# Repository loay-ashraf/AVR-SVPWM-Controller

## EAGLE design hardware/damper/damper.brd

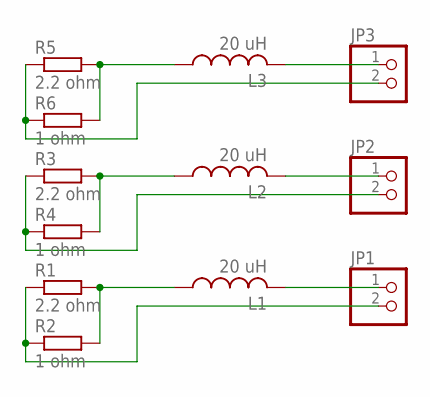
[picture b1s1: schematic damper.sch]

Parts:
JP1, JP2, JP3: PINHD-1X2; 1X02
L1, L2, L3: 20 uH; 0207/10
R1, R3, R5: 2.2 ohm; VTA52
R2, R4, R6: 1 ohm; VTA52

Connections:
unnamed: L1.1, R1.2, R2.2
unnamed: JP1.1, L1.2
unnamed: JP1.2, R1.1, R2.1
unnamed: L2.1, R3.2, R4.2
unnamed: JP2.1, L2.2
unnamed: JP2.2, R3.1, R4.1
unnamed: L3.1, R5.2, R6.2
unnamed: JP3.1, L3.2
unnamed: JP3.2, R5.1, R6.1

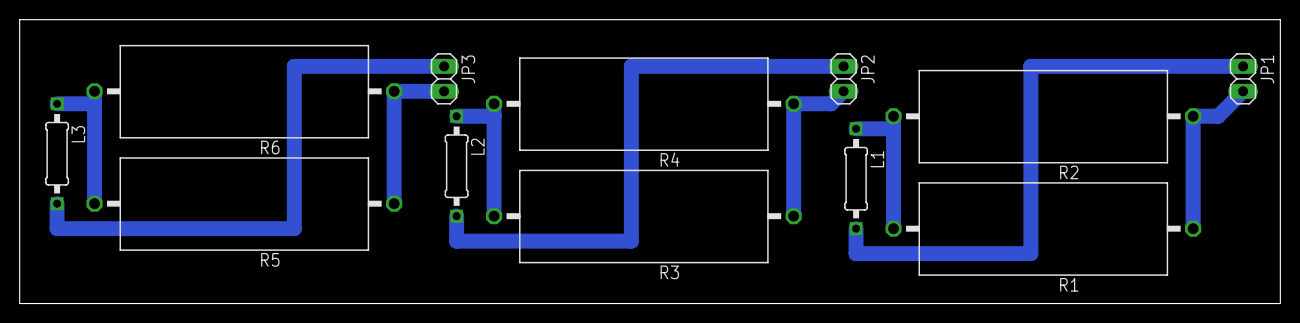
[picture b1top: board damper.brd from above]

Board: 2 copper layers, 128.2 x 28.9 mm, 12 parts (0 on the bottom side), 9 nets.

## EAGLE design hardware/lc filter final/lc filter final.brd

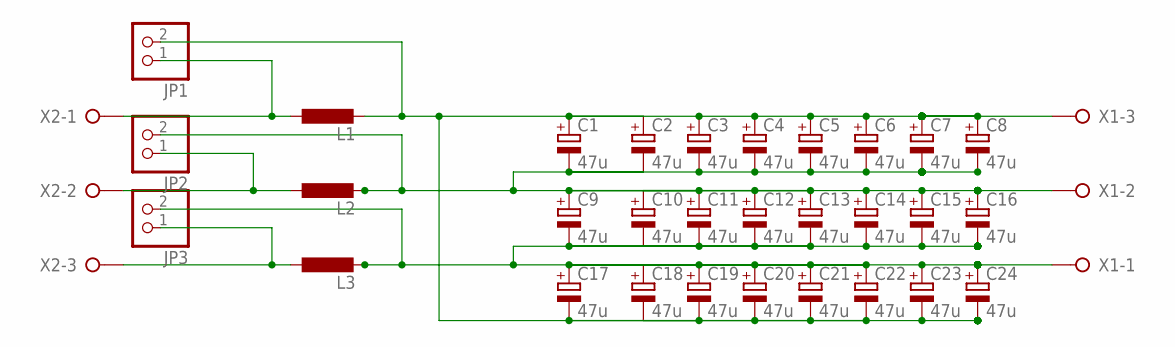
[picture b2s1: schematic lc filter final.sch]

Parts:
C1, C2, C3, C4, C5, C6, C7, C8, C9, C10, C11, C12, C13, C14, C15, C16, C17, C18, C19, C20, C21, C22, C23, C24: 47u; E5-10,5
JP1, JP2, JP3: PINHD-1X2; 1X02
L1, L2, L3: L-EU6000-XXX-RC; 6000-XXXX-RC
X1, X2: W237-03P; W237-133

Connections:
unnamed: JP1.1, L1.1, X2.1
unnamed: C1.-, C2.-, C3.-, C4.-, C5.-, C6.-, C7.-, C8.-, C9.+, C10.+, C11.+, C12.+, C13.+, C14.+, C15.+, C16.+, JP2.2, L2.2, X1.2
unnamed: JP2.1, L2.1, X2.2
unnamed: C9.-, C10.-, C11.-, C12.-, C13.-, C14.-, C15.-, C16.-, C17.+, C18.+, C19.+, C20.+, C21.+, C22.+, C23.+, C24.+, JP3.2, L3.2, X1.1
unnamed: JP3.1, L3.1, X2.3
unnamed: C1.+, C2.+, C3.+, C4.+, C5.+, C6.+, C7.+, C8.+, C17.-, C18.-, C19.-, C20.-, C21.-, C22.-, C23.-, C24.-, JP1.2, L1.2, X1.3

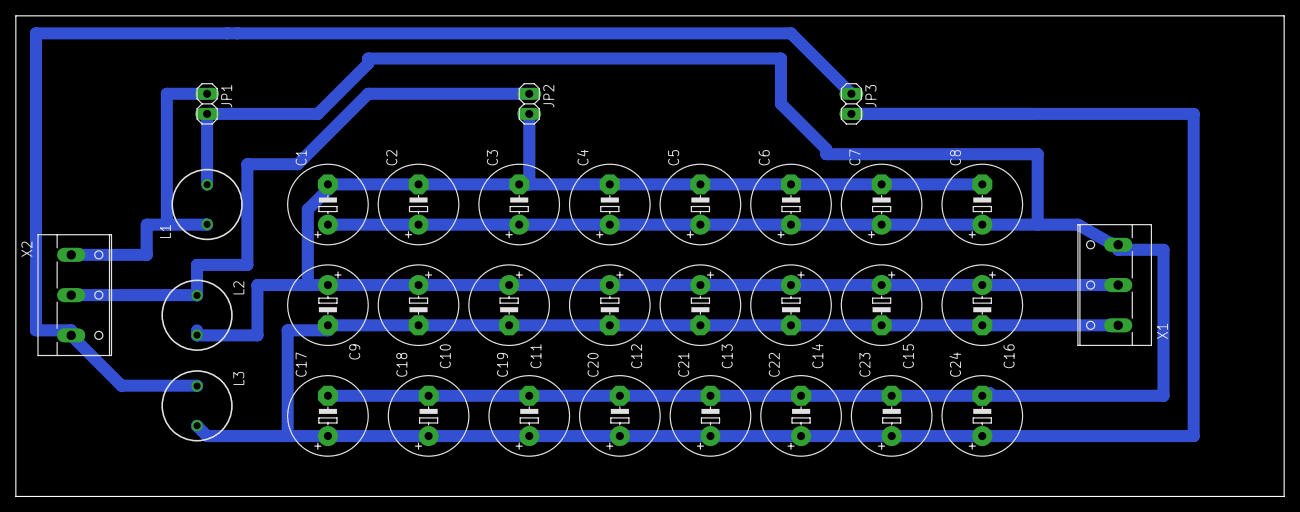
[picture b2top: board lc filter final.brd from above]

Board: 2 copper layers, 160.0 x 60.6 mm, 32 parts (0 on the bottom side), 6 nets.
